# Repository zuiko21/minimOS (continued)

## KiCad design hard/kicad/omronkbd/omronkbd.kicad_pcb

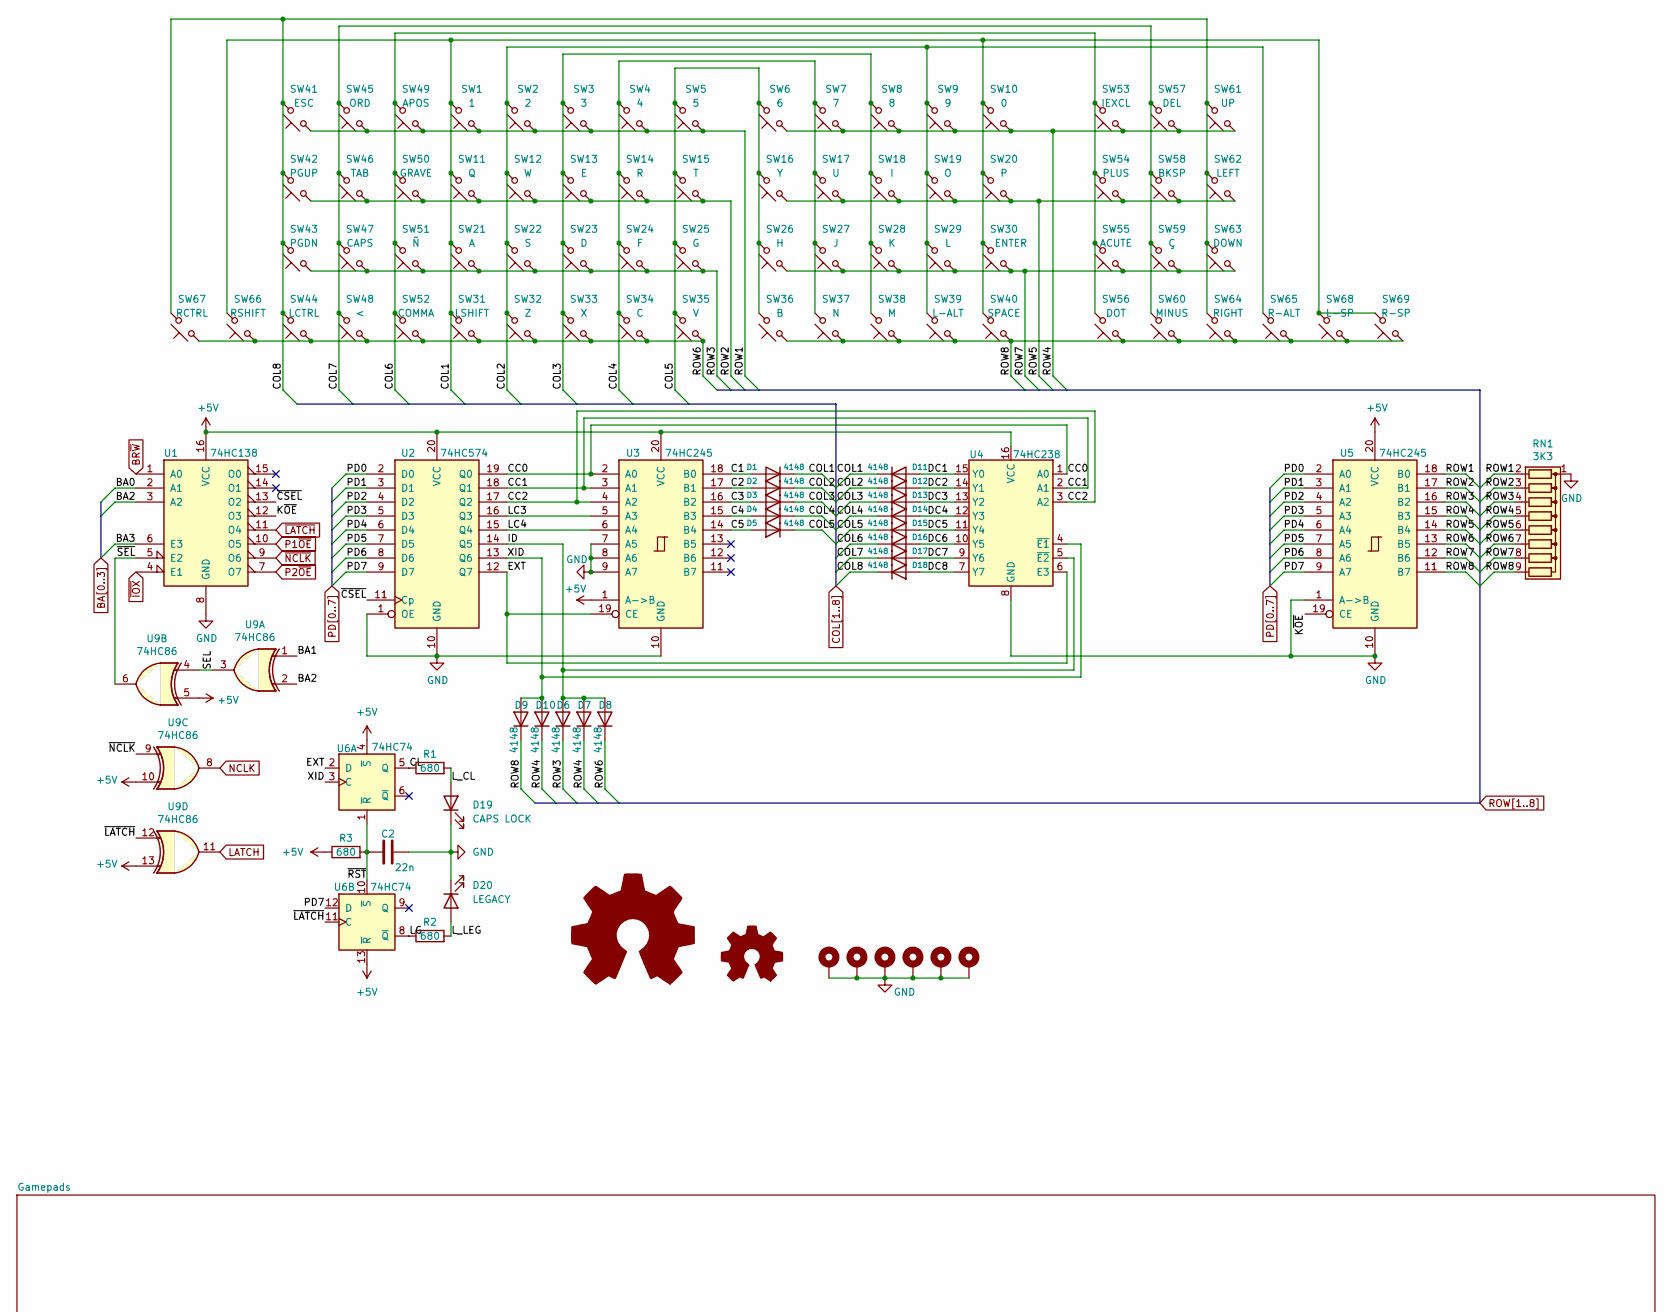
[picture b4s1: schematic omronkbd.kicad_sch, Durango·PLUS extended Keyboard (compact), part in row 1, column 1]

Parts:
C2: 22n; C_Disc_D5.0mm_W2.5mm_P5.00mm
D1, D2, D3, D4, D5, D6, D7, D8, D9, D10, D11, D12, D13, D14, D15, D16, D17, D18: 4148; D_DO-34_SOD68_P7.62mm_Horizontal
D19: CAPS LOCK; LED_D3.0mm
D20: LEGACY; LED_D3.0mm
H1, H2, H3, H4, H5, H6: MountingHole_Pad; MountingHole_3.2mm_M3_DIN965_Pad
LOGO1: OSHW-Logo2_24.3x20mm_SilkScreen
LOGO2: Logo_Open_Hardware_Small; j300
R1, R2, R3: 680; R_Axial_DIN0207_L6.3mm_D2.5mm_P10.16mm_Horizontal
RN1: 3K3; R_Array_SIP9
SW1: 1; SW_SPST_Omron_B3F-40xx
SW2: 2; SW_SPST_Omron_B3F-40xx
SW3: 3; SW_SPST_Omron_B3F-40xx
SW4: 4; SW_SPST_Omron_B3F-40xx
SW5: 5; SW_SPST_Omron_B3F-40xx
SW6: 6; SW_SPST_Omron_B3F-40xx
SW7: 7; SW_SPST_Omron_B3F-40xx
SW8: 8; SW_SPST_Omron_B3F-40xx
SW9: 9; SW_SPST_Omron_B3F-40xx
SW10: 0; SW_SPST_Omron_B3F-40xx
SW11: Q; SW_SPST_Omron_B3F-40xx
SW12: W; SW_SPST_Omron_B3F-40xx
SW13: E; SW_SPST_Omron_B3F-40xx
SW14: R; SW_SPST_Omron_B3F-40xx
SW15: T; SW_SPST_Omron_B3F-40xx
SW16: Y; SW_SPST_Omron_B3F-40xx
SW17: U; SW_SPST_Omron_B3F-40xx
SW18: I; SW_SPST_Omron_B3F-40xx
SW19: O; SW_SPST_Omron_B3F-40xx
SW20: P; SW_SPST_Omron_B3F-40xx
SW21: A; SW_SPST_Omron_B3F-40xx
SW22: S; SW_SPST_Omron_B3F-40xx
SW23: D; SW_SPST_Omron_B3F-40xx
SW24: F; SW_SPST_Omron_B3F-40xx
SW25: G; SW_SPST_Omron_B3F-40xx
SW26: H; SW_SPST_Omron_B3F-40xx
SW27: J; SW_SPST_Omron_B3F-40xx
SW28: K; SW_SPST_Omron_B3F-40xx
SW29: L; SW_SPST_Omron_B3F-40xx
SW30: ENTER; SW_SPST_Omron_B3F-40xx
SW31: LSHIFT; SW_SPST_Omron_B3F-40xx
SW32: Z; SW_SPST_Omron_B3F-40xx
SW33: X; SW_SPST_Omron_B3F-40xx
SW34: C; SW_SPST_Omron_B3F-40xx
SW35: V; SW_SPST_Omron_B3F-40xx
SW36: B; SW_SPST_Omron_B3F-40xx
SW37: N; SW_SPST_Omron_B3F-40xx
SW38: M; SW_SPST_Omron_B3F-40xx
SW39: L-ALT; SW_SPST_Omron_B3F-40xx
SW40: SPACE; SW_SPST_Omron_B3F-40xx
SW41: ESC; SW_SPST_Omron_B3F-40xx
SW42: PGUP; SW_SPST_Omron_B3F-40xx
SW43: PGDN; SW_SPST_Omron_B3F-40xx
SW44: LCTRL; SW_SPST_Omron_B3F-40xx
SW45: ORD; SW_SPST_Omron_B3F-40xx
SW46: TAB; SW_SPST_Omron_B3F-40xx
SW47: CAPS; SW_SPST_Omron_B3F-40xx
SW48: <; SW_SPST_Omron_B3F-40xx
SW49: APOS; SW_SPST_Omron_B3F-40xx
SW50: GRAVE; SW_SPST_Omron_B3F-40xx
SW51: Ñ; SW_SPST_Omron_B3F-40xx
SW52: COMMA; SW_SPST_Omron_B3F-40xx
SW53: IEXCL; SW_SPST_Omron_B3F-40xx
SW54: PLUS; SW_SPST_Omron_B3F-40xx
SW55: ACUTE; SW_SPST_Omron_B3F-40xx
SW56: DOT; SW_SPST_Omron_B3F-40xx
SW57: DEL; SW_SPST_Omron_B3F-40xx
SW58: BKSP; SW_SPST_Omron_B3F-40xx
SW59: Ç; SW_SPST_Omron_B3F-40xx
SW60: MINUS; SW_SPST_Omron_B3F-40xx
SW61: UP; SW_SPST_Omron_B3F-40xx
SW62: LEFT; SW_SPST_Omron_B3F-40xx
SW63: DOWN; SW_SPST_Omron_B3F-40xx
SW64: RIGHT; SW_SPST_Omron_B3F-40xx
SW65: R-ALT; SW_SPST_Omron_B3F-40xx
SW66: RSHIFT; SW_SPST_Omron_B3F-40xx
SW67: RCTRL; SW_SPST_Omron_B3F-40xx
SW68: L-SP; SW_SPST_Omron_B3F-40xx
SW69: R-SP; SW_SPST_Omron_B3F-40xx
U1: 74HC138; DIP-16_W7.62mm_Socket
U2: 74HC574; DIP-20_W7.62mm_Socket
U3, U5: 74HC245; DIP-20_W7.62mm_Socket
U4: 74HC238; DIP-16_W7.62mm_Socket
U6: 74HC74; DIP-14_W7.62mm_Socket
U9: 74HC86; DIP-14_W7.62mm_Socket

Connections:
+5V: R3.1, U1.16 (VCC), U2.20 (VCC), U3.1 (A->B), U3.20 (VCC), U4.16 (VCC), U5.20 (VCC), U6.4 (~S), U6.13 (~R), U6.14 (VCC), U9.5, U9.10, U9.13, U9.14 (VCC); also elsewhere on the board
/C1: D1.2 (A), U3.18 (B0)
/C2: D2.2 (A), U3.17 (B1)
/C3: D3.2 (A), U3.16 (B2)
/C4: D4.2 (A), U3.15 (B3)
/C5: D5.2 (A), U3.14 (B4)
/CC0: U2.19 (Q0), U3.2 (A0), U4.1 (A0)
/CC1: U2.18 (Q1), U3.3 (A1), U4.2 (A1)
/CC2: U2.17 (Q2), U3.4 (A2), U4.3 (A2)
/CL: R1.1, U6.5 (Q)
/DC1: D11.2 (A), U4.15 (Y0)
/DC2: D12.2 (A), U4.14 (Y1)
/DC3: D13.2 (A), U4.13 (Y2)
/DC4: D14.2 (A), U4.12 (Y3)
/DC5: D15.2 (A), U4.11 (Y4)
/DC6: D16.2 (A), U4.10 (Y5)
/DC7: D17.2 (A), U4.9 (Y6)
/DC8: D18.2 (A), U4.7 (Y7)
/EXT: U2.12 (Q7), U3.19 (CE), U4.6 (E3), U6.2 (D)
/ID: D6.2 (A), D7.2 (A), D8.2 (A), U2.14 (Q5), U4.5 (~E2)
/K~OE: U1.12 (O3), U5.19 (CE)
/LC3: U2.16 (Q3), U3.5 (A3)
/LC4: U2.15 (Q4), U3.6 (A4)
/LG: R2.1, U6.8 (~Q)
/L_CL: D19.2 (A), R1.2
/L_LEG: D20.2 (A), R2.2
/SEL: U9.3, U9.4
/XID: D9.2 (A), D10.2 (A), U2.13 (Q6), U4.4 (~E1), U6.3 (C)
/~CSEL: U1.13 (O2), U2.11 (Cp)
/~RST: C2.1, R3.2, U6.1 (~R), U6.10 (~S)
/~SEL: U1.5 (E2), U9.6
BA0: U1.2 (A1); also elsewhere on the board
BA1: U9.1; also elsewhere on the board
BA2: U1.3 (A2), U9.2; also elsewhere on the board
BA3: U1.6 (E3); also elsewhere on the board
BR~W: U1.1 (A0); also elsewhere on the board
COL1: D1.1 (K), D11.1 (K), SW1.2, SW10.2, SW11.2, SW20.2, SW21.2, SW30.2, SW31.2, SW40.2, SW66.2, SW68.2, SW69.2
COL2: D2.1 (K), D12.1 (K), SW2.2, SW9.2, SW12.2, SW19.2, SW22.2, SW29.2, SW32.2, SW39.2, SW65.2
COL3: D3.1 (K), D13.1 (K), SW3.2, SW8.2, SW13.2, SW18.2, SW23.2, SW28.2, SW33.2, SW38.2
COL4: D4.1 (K), D14.1 (K), SW4.2, SW7.2, SW14.2, SW17.2, SW24.2, SW27.2, SW34.2, SW37.2
COL5: D5.1 (K), D15.1 (K), SW5.2, SW6.2, SW15.2, SW16.2, SW25.2, SW26.2, SW35.2, SW36.2
COL6: D16.1 (K), SW49.2, SW50.2, SW51.2, SW52.2, SW53.2, SW54.2, SW55.2, SW56.2
COL7: D17.1 (K), SW45.2, SW46.2, SW47.2, SW48.2, SW57.2, SW58.2, SW59.2, SW60.2
COL8: D18.1 (K), SW41.2, SW42.2, SW43.2, SW44.2, SW61.2, SW62.2, SW63.2, SW64.2, SW67.2
GND: C2.2, D19.1 (K), D20.1 (K), H1.1, H2.1, H3.1, H4.1, H5.1, H6.1, RN1.1 (common), U1.8 (GND), U2.1 (OE), U2.10 (GND), U3.7 (A5), U3.8 (A6), U3.9 (A7), U3.10 (GND), U4.8 (GND), U5.1 (A->B), U5.10 (GND), U6.7 (GND), U9.7 (GND); also elsewhere on the board
LATCH: U9.11; also elsewhere on the board
NCLK: U9.8; also elsewhere on the board
P1~OE: U1.10 (O5); also elsewhere on the board
P2~OE: U1.7 (O7); also elsewhere on the board
PD0: U2.2 (D0), U5.2 (A0); also elsewhere on the board
PD1: U2.3 (D1), U5.3 (A1); also elsewhere on the board
PD2: U2.4 (D2), U5.4 (A2); also elsewhere on the board
PD3: U2.5 (D3), U5.5 (A3); also elsewhere on the board
PD4: U2.6 (D4), U5.6 (A4); also elsewhere on the board
PD5: U2.7 (D5), U5.7 (A5); also elsewhere on the board
PD6: U2.8 (D6), U5.8 (A6); also elsewhere on the board
PD7: U2.9 (D7), U5.9 (A7), U6.12 (D); also elsewhere on the board
ROW1: RN1.2 (R1), SW1.1, SW2.1, SW3.1, SW4.1, SW5.1, SW41.1, SW45.1, SW49.1, U5.18 (B0)
ROW2: RN1.3 (R2), SW11.1, SW12.1, SW13.1, SW14.1, SW15.1, SW42.1, SW46.1, SW50.1, U5.17 (B1)
ROW3: D6.1 (K), RN1.4 (R3), SW21.1, SW22.1, SW23.1, SW24.1, SW25.1, SW43.1, SW47.1, SW51.1, U5.16 (B2)
ROW4: D7.1 (K), D10.1 (K), RN1.5 (R4), SW6.1, SW7.1, SW8.1, SW9.1, SW10.1, SW53.1, SW57.1, SW61.1, U5.15 (B3)
ROW5: RN1.6 (R5), SW16.1, SW17.1, SW18.1, SW19.1, SW20.1, SW54.1, SW58.1, SW62.1, U5.14 (B4)
ROW6: D8.1 (K), RN1.7 (R6), SW31.1, SW32.1, SW33.1, SW34.1, SW35.1, SW44.1, SW48.1, SW52.1, SW66.1, SW67.1, U5.13 (B5)
ROW7: RN1.8 (R7), SW26.1, SW27.1, SW28.1, SW29.1, SW30.1, SW55.1, SW59.1, SW63.1, U5.12 (B6)
ROW8: D9.1 (K), RN1.9 (R8), SW36.1, SW37.1, SW38.1, SW39.1, SW40.1, SW56.1, SW60.1, SW64.1, SW65.1, SW68.1, SW69.1, U5.11 (B7)
~IOX: U1.4 (E1); also elsewhere on the board
~LATCH: U1.11 (O4), U6.11 (C), U9.12; also elsewhere on the board
~NCLK: U1.9 (O6), U9.9; also elsewhere on the board

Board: 2 copper layers, 125 parts (0 on the bottom side), 87 nets, no tracks yet.

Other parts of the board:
C1: 22n; C_Disc_D5.0mm_W2.5mm_P5.00mm
J1: TO COMPUTER; PinSocket_2x08_P2.54mm_Vertical
J2, J3: IOx; IDC-Header_2x08_P2.54mm_Vertical
J101: MD/VCS1; DSUB-9_Male_Horizontal_P2.77x2.84mm_EdgePinOffset4.94mm_Hou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
J102: MD/VCS2; DSUB-9_Male_Horizontal_P2.77x2.84mm_EdgePinOffset4.94mm_Hou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
J201: NES 1; NES gamepad
J202: NES 2; NES gamepad
JP1: MD/VCS; SolderJumper-3_P1.3mm_Bridged12_RoundedPad1.0x1.5mm
RN2, RN101: 22K; R_Array_SIP9
U101, U102: 74HC245; DIP-20_W7.62mm_Socket
U103: 74HC174; DIP-16_W7.62mm_Socket
U201, U202: 74HC595; DIP-16_W7.62mm_Socket

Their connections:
+5V: C1.1, J1.1, J2.1, J3.1, J101.5, J102.5, J201.6, J202.6, JP1.1 (A), RN2.1 (common), RN101.1 (common), U101.20 (VCC), U102.20 (VCC), U103.3 (D0), U103.14 (D5), U103.16 (VCC), U201.10 (~SRCLR), U201.16 (VCC), U202.10 (~SRCLR), U202.16 (VCC); also elsewhere on the board
/Gamepads/VCS: JP1.2 (C), U103.1 (~Mr)
/Gamepads/~A1: U101.11 (B7), U103.7 (Q2)
/Gamepads/~A2: U102.11 (B7), U103.10 (Q3)
/Gamepads/~AB1: J101.6, RN101.8 (R7), U101.13 (B5), U103.6 (D2)
/Gamepads/~AB2: J102.6, RN2.8 (R7), U102.13 (B5), U103.11 (D3)
/Gamepads/~DAT1: J201.1, RN2.2 (R1), U201.14 (SER)
/Gamepads/~DAT2: J202.1, RN2.7 (R6), U202.14 (SER)
/Gamepads/~DN1: J101.2, RN101.4 (R3), U101.17 (B1)
/Gamepads/~DN2: J102.2, RN2.4 (R3), U102.17 (B1)
/Gamepads/~LT1: J101.3, RN101.5 (R4), U101.16 (B2)
/Gamepads/~LT2: J102.3, RN2.5 (R4), U102.16 (B2)
/Gamepads/~RT1: J101.4, RN101.3 (R2), U101.18 (B0)
/Gamepads/~RT2: J102.4, RN2.3 (R2), U102.18 (B0)
/Gamepads/~S1: U101.12 (B6), U103.5 (Q1)
/Gamepads/~S2: U102.12 (B6), U103.12 (Q4)
/Gamepads/~SC1: J101.9, RN101.9 (R8), U101.14 (B4), U103.4 (D1)
/Gamepads/~SC2: J102.9, RN2.9 (R8), U102.14 (B4), U103.13 (D4)
/Gamepads/~UP1: J101.1, RN101.6 (R5), U101.15 (B3)
/Gamepads/~UP2: J102.1, RN2.6 (R5), U102.15 (B3)
BA0: J1.3, J2.3, J3.3; also elsewhere on the board
BA1: J1.5, J2.5, J3.5; also elsewhere on the board
BA2: J1.7, J2.7, J3.7; also elsewhere on the board
BA3: J1.9, J2.9, J3.9; also elsewhere on the board
BR~W: J1.11, J2.11, J3.11; also elsewhere on the board
GND: C1.2, J1.15, J2.15, J3.15, J101.8, J102.8, J201.7, J202.7, JP1.3 (B), U101.1 (A->B), U101.10 (GND), U102.1 (A->B), U102.10 (GND), U103.8 (GND), U201.8 (GND), U202.8 (GND); also elsewhere on the board
LATCH: J201.3, J202.3; also elsewhere on the board
NCLK: J201.5, J202.5, U201.11 (SRCLK), U202.11 (SRCLK); also elsewhere on the board
P1~OE: U101.19 (CE), U201.13 (~OE); also elsewhere on the board
P2~OE: U102.19 (CE), U202.13 (~OE); also elsewhere on the board
PD0: J1.2, J2.2, J3.2, U101.2 (A0), U102.2 (A0), U201.15 (QA), U202.15 (QA); also elsewhere on the board
PD1: J1.4, J2.4, J3.4, U101.3 (A1), U102.3 (A1), U201.2 (QC), U202.2 (QC); also elsewhere on the board
PD2: J1.6, J2.6, J3.6, U101.4 (A2), U102.4 (A2), U201.1 (QB), U202.1 (QB); also elsewhere on the board
PD3: J1.8, J2.8, J3.8, U101.5 (A3), U102.5 (A3), U201.3 (QD), U202.3 (QD); also elsewhere on the board
PD4: J1.10, J2.10, J3.10, U101.6 (A4), U102.6 (A4), U201.5 (QF), U202.5 (QF); also elsewhere on the board
PD5: J1.12, J2.12, J3.12, U101.7 (A5), U102.7 (A5), U201.6 (QG), U202.6 (QG); also elsewhere on the board
PD6: J1.14, J2.14, J3.14, U101.8 (A6), U102.8 (A6), U201.4 (QE), U202.4 (QE); also elsewhere on the board
PD7: J1.16, J2.16, J3.16, U101.9 (A7), U102.9 (A7), U201.7 (QH), U202.7 (QH); also elsewhere on the board
~IOX: J1.13, J2.13, J3.13; also elsewhere on the board
~LATCH: J101.7, J102.7, U103.9 (Cp); also elsewhere on the board
~NCLK: U201.12 (RCLK), U202.12 (RCLK); also elsewhere on the board

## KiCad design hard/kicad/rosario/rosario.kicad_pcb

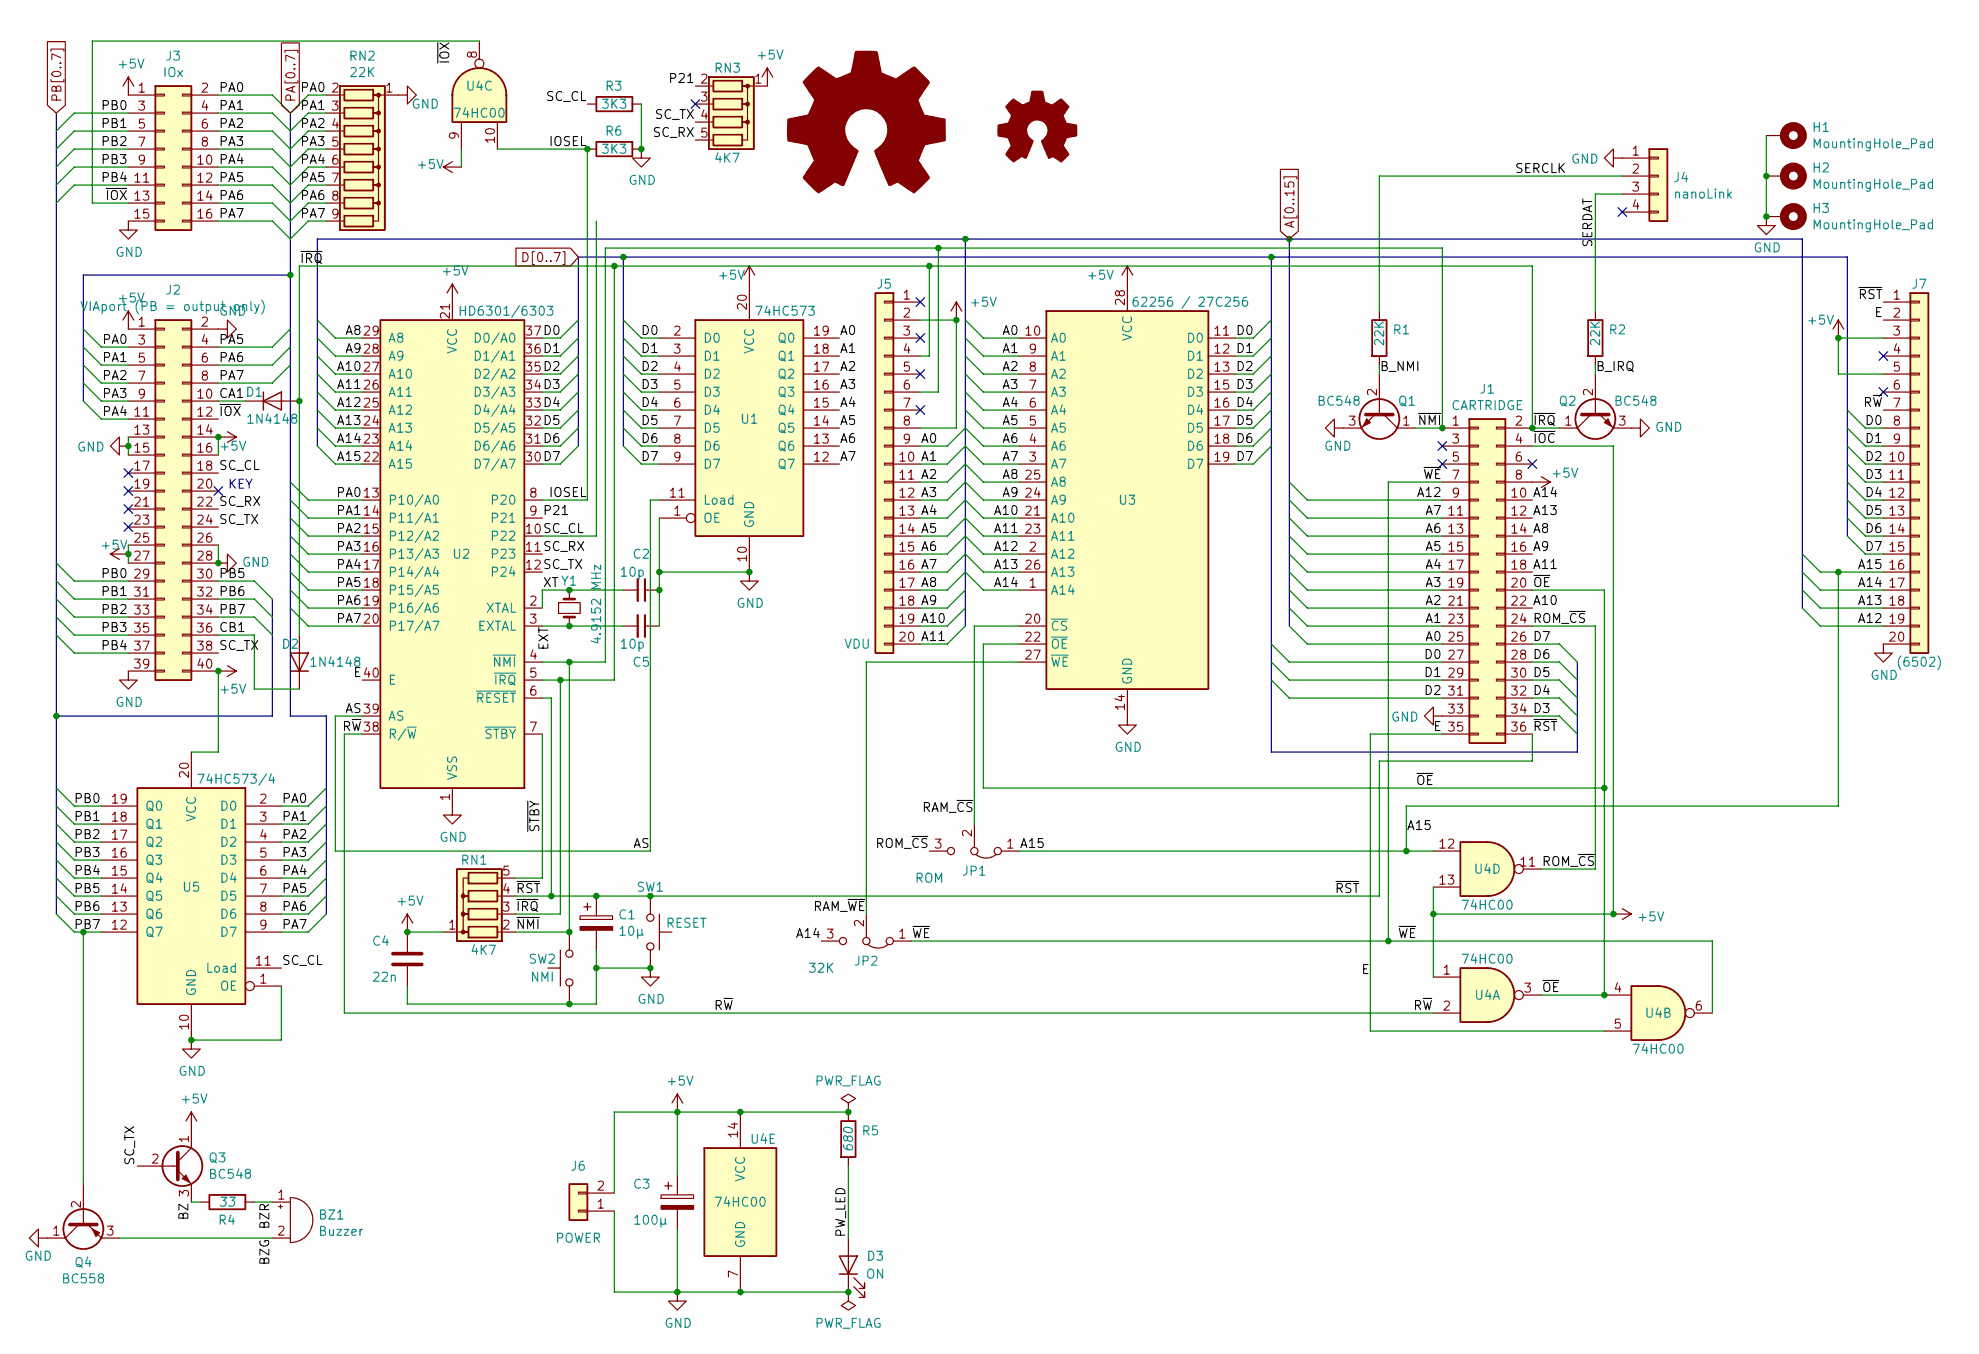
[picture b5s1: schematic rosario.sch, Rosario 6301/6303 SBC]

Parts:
BZ1: Buzzer; Buzzer_12x9.5RM7.6
C1: 10µ; CP_Radial_D4.0mm_P1.50mm
C2, C5: 10p; C_Disc_D3.8mm_W2.6mm_P2.50mm
C3: 100µ; CP_Radial_D4.0mm_P1.50mm
C4: 22n; C_Rect_L7.2mm_W2.5mm_P5.00mm_FKS2_FKP2_MKS2_MKP2
D1, D2: 1N4148; D_DO-35_SOD27_P2.54mm_Vertical_AnodeUp
D3: ON; LED_D3.0mm
H1, H2, H3: MountingHole_Pad; MountingHole_3.2mm_M3_DIN965_Pad
J1: CARTRIDGE; PinSocket_2x18_EDGE
J2: VIAport (PB = output only); IDC-Header_2x20_P2.54mm_Vertical
J3: IOx; IDC-Header_2x08_P2.54mm_Vertical
J4: nanoLink; PinHeader_1x04_P2.54mm_Vertical
J5: VDU; PinSocket_1x20_P2.54mm_Vertical
J6: POWER; JST_EH_S2B-EH_1x02_P2.50mm_Horizontal
J7: (6502); PinSocket_1x20_P2.54mm_Vertical
JP1: ROM; SolderJumper-3_P1.3mm_Bridged12_RoundedPad1.0x1.5mm
JP2: 32K; SolderJumper-3_P1.3mm_Bridged12_RoundedPad1.0x1.5mm
LOGO1: Logo_Open_Hardware_Large; OSHW-Symbol_8.9x8mm_SilkScreen
LOGO2: Logo_Open_Hardware_Small; jaqueria
Q1, Q2, Q3: BC548; TO-92_Inline
Q4: BC558; TO-92_Inline
R1, R2: 22K; R_Axial_DIN0207_L6.3mm_D2.5mm_P2.54mm_Vertical
R3, R6: 3K3; R_Axial_DIN0207_L6.3mm_D2.5mm_P2.54mm_Vertical
R4: 33; R_Axial_DIN0309_L9.0mm_D3.2mm_P2.54mm_Vertical
R5: 680; R_Axial_DIN0207_L6.3mm_D2.5mm_P2.54mm_Vertical
RN1, RN3: 4K7; R_Array_SIP5
RN2: 22K; R_Array_SIP9
SW1: RESET; SW_PUSH_6mm
SW2: NMI; SW_PUSH_6mm
U1: 74HC573; DIP-20_W7.62mm_Socket
U2: HD6301/6303; DIP-40_W15.24mm_Socket
U3: 62256 / 27C256; DIP-28_W15.24mm_Socket
U4: 74HC00; DIP-14_W7.62mm_Socket
U5: 74HC573/4; DIP-20_W7.62mm_Socket
Y1: 4.9152 MHz; Crystal_HC49-U_Vertical

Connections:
/AS: U1.11 (Load), U2.39 (AS)
/BZ: Q3.3 (E), R4.1
/BZG: BZ1.2 (+), Q4.3 (E)
/BZR: BZ1.1 (-), R4.2
/B_IRQ: Q2.2 (B), R2.2
/B_NMI: Q1.2 (B), R1.2
/CA1: D1.1 (K), J2.10
/CB1: D2.1 (K), J2.36
/EXT: C5.2, U2.3 (EXTAL), Y1.2
/IOSEL: R6.1, U2.8 (P20), U4.10
/P21: RN3.2 (R1), U2.9 (P21)
/PW_LED: D3.2 (A), R5.2
/RAM_~CS: JP1.2 (C), U3.20 (~CS)
/RAM_~WE: JP2.2 (C), U3.27 (~WE)
/ROM_~CS: J1.24, JP1.3 (B), U4.11
/R~W: J7.7, U2.38 (R/~W), U4.2
/SC_CL: J2.18, R3.1, U2.10 (P22), U5.11 (Load)
/SC_RX: J2.22, RN3.5 (R4), U2.11 (P23)
/SC_TX: J2.24, J2.38, Q3.2 (B), RN3.4 (R3), U2.12 (P24)
/SERCLK: J4.2, R1.1
/SERDAT: J4.3, R2.1
/XT: C2.2, U2.2 (XTAL), Y1.1
/~IOX: J2.12, J3.13, U4.8
/~IRQ: D1.2 (A), D2.2 (A), J1.2, J5.4, Q2.1 (C), RN1.3 (R2), U2.5 (~IRQ)
/~NMI: J1.1, J5.6, Q1.1 (C), RN1.2 (R1), SW2.2, U2.4 (~NMI)
/~OE: J1.20, U3.22 (~OE), U4.3, U4.4
/~RST: C1.1, J1.36, J7.1, RN1.4 (R3), SW1.2, U2.6 (~RESET)
/~STBY: RN1.5 (R4), U2.7 (~STBY)
/~WE: J1.7, JP2.1 (A), U4.6
A0: J1.25, J5.9, U1.19 (Q0), U3.10 (A0)
A1: J1.23, J5.10, U1.18 (Q1), U3.9 (A1)
A2: J1.21, J5.11, U1.17 (Q2), U3.8 (A2)
A3: J1.19, J5.12, U1.16 (Q3), U3.7 (A3)
A4: J1.17, J5.13, U1.15 (Q4), U3.6 (A4)
A5: J1.15, J5.14, U1.14 (Q5), U3.5 (A5)
A6: J1.13, J5.15, U1.13 (Q6), U3.4 (A6)
A7: J1.11, J5.16, U1.12 (Q7), U3.3 (A7)
A8: J1.14, J5.17, U2.29 (A8), U3.25 (A8)
A9: J1.16, J5.18, U2.28 (A9), U3.24 (A9)
A10: J1.22, J5.19, U2.27 (A10), U3.21 (A10)
A11: J1.18, J5.20, U2.26 (A11), U3.23 (A11)
A12: J1.9, J7.19, U2.25 (A12), U3.2 (A12)
A13: J1.12, J7.18, U2.24 (A13), U3.26 (A13)
A14: J1.10, J7.17, JP2.3 (B), U2.23 (A14), U3.1 (A14)
A15: J7.16, JP1.1 (A), U2.22 (A15), U4.12
D0: J1.27, J7.8, U1.2 (D0), U2.37 (D0/A0), U3.11 (D0)
D1: J1.29, J7.9, U1.3 (D1), U2.36 (D1/A1), U3.12 (D1)
D2: J1.31, J7.10, U1.4 (D2), U2.35 (D2/A2), U3.13 (D2)
D3: J1.34, J7.11, U1.5 (D3), U2.34 (D3/A3), U3.15 (D3)
D4: J1.32, J7.12, U1.6 (D4), U2.33 (D4/A4), U3.16 (D4)
D5: J1.30, J7.13, U1.7 (D5), U2.32 (D5/A5), U3.17 (D5)
D6: J1.28, J7.14, U1.8 (D6), U2.31 (D6/A6), U3.18 (D6)
D7: J1.26, J7.15, U1.9 (D7), U2.30 (D7/A7), U3.19 (D7)
GND: C1.2, C2.1, C3.2, C4.2, C5.1, D3.1 (K), H1.1, H2.1, H3.1, J1.33, J2.2, J2.13, J2.15, J2.26, J2.28, J2.39, J3.15, J4.1, J6.1, J7.20, Q1.3 (E), Q2.3 (E), Q4.1 (C), R3.2, R6.2, RN2.1 (common), SW1.1, SW2.1, U1.1 (OE), U1.10 (GND), U2.1 (VSS), U3.14 (GND), U4.7 (GND), U5.1 (OE), U5.10 (GND)
PA0: J2.3, J3.2, RN2.2 (R1), U2.13 (P10/A0), U5.2 (D0)
PA1: J2.5, J3.4, RN2.3 (R2), U2.14 (P11/A1), U5.3 (D1)
PA2: J2.7, J3.6, RN2.4 (R3), U2.15 (P12/A2), U5.4 (D2)
PA3: J2.9, J3.8, RN2.5 (R4), U2.16 (P13/A3), U5.5 (D3)
PA4: J2.11, J3.10, RN2.6 (R5), U2.17 (P14/A4), U5.6 (D4)
PA5: J2.4, J3.12, RN2.7 (R6), U2.18 (P15/A5), U5.7 (D5)
PA6: J2.6, J3.14, RN2.8 (R7), U2.19 (P16/A6), U5.8 (D6)
PA7: J2.8, J3.16, RN2.9 (R8), U2.20 (P17/A7), U5.9 (D7)
PB0: J2.29, J3.3, U5.19 (Q0)
PB1: J2.31, J3.5, U5.18 (Q1)
PB2: J2.33, J3.7, U5.17 (Q2)
PB3: J2.35, J3.9, U5.16 (Q3)
PB4: J2.37, J3.11, U5.15 (Q4)
PB5: J2.30, U5.14 (Q5)
PB6: J2.32, U5.13 (Q6)
PB7: J2.34, Q4.2 (B), U5.12 (Q7)

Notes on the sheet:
KEY

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
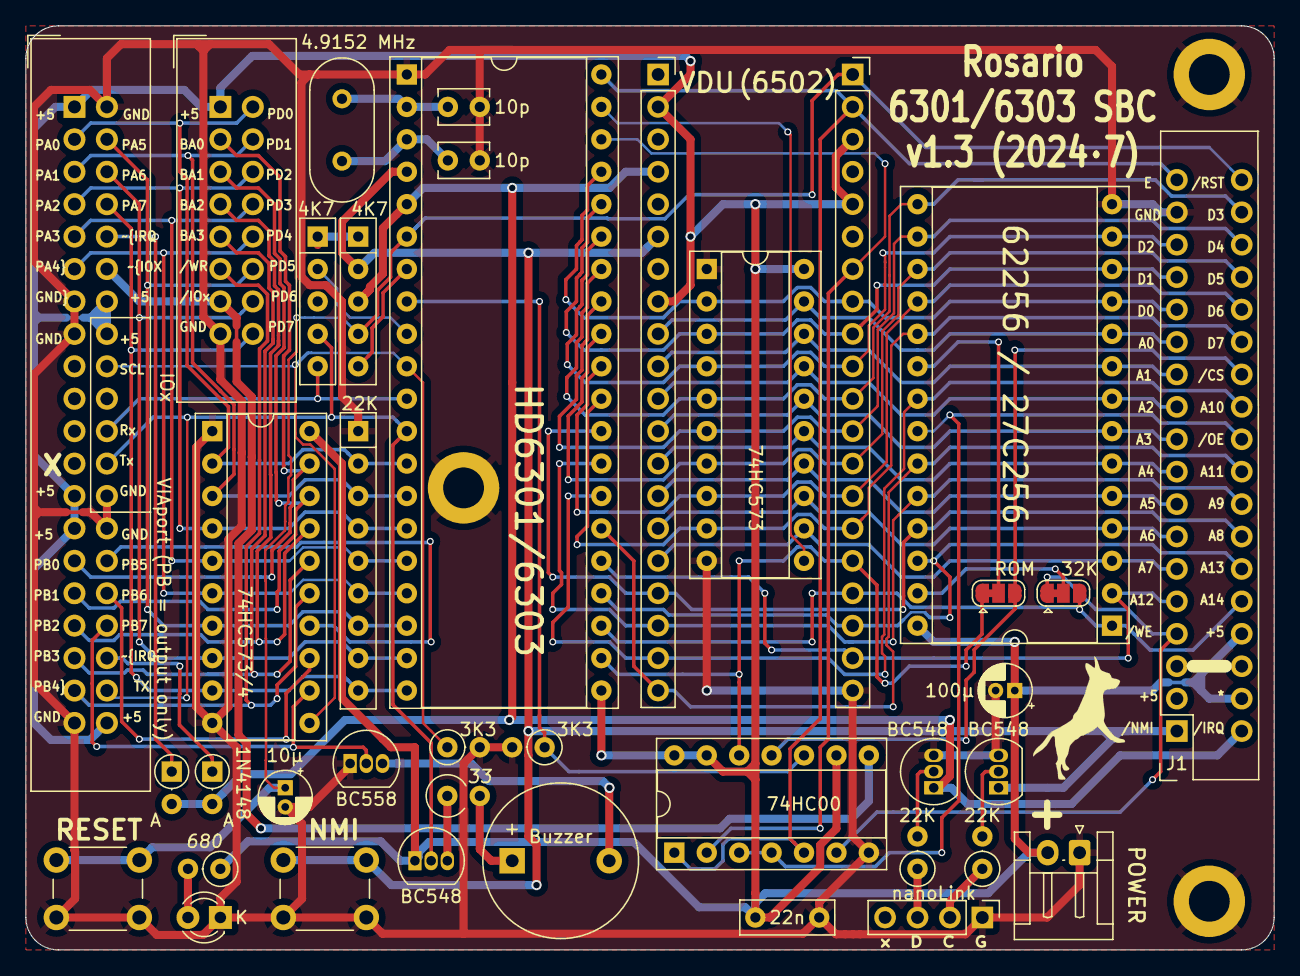
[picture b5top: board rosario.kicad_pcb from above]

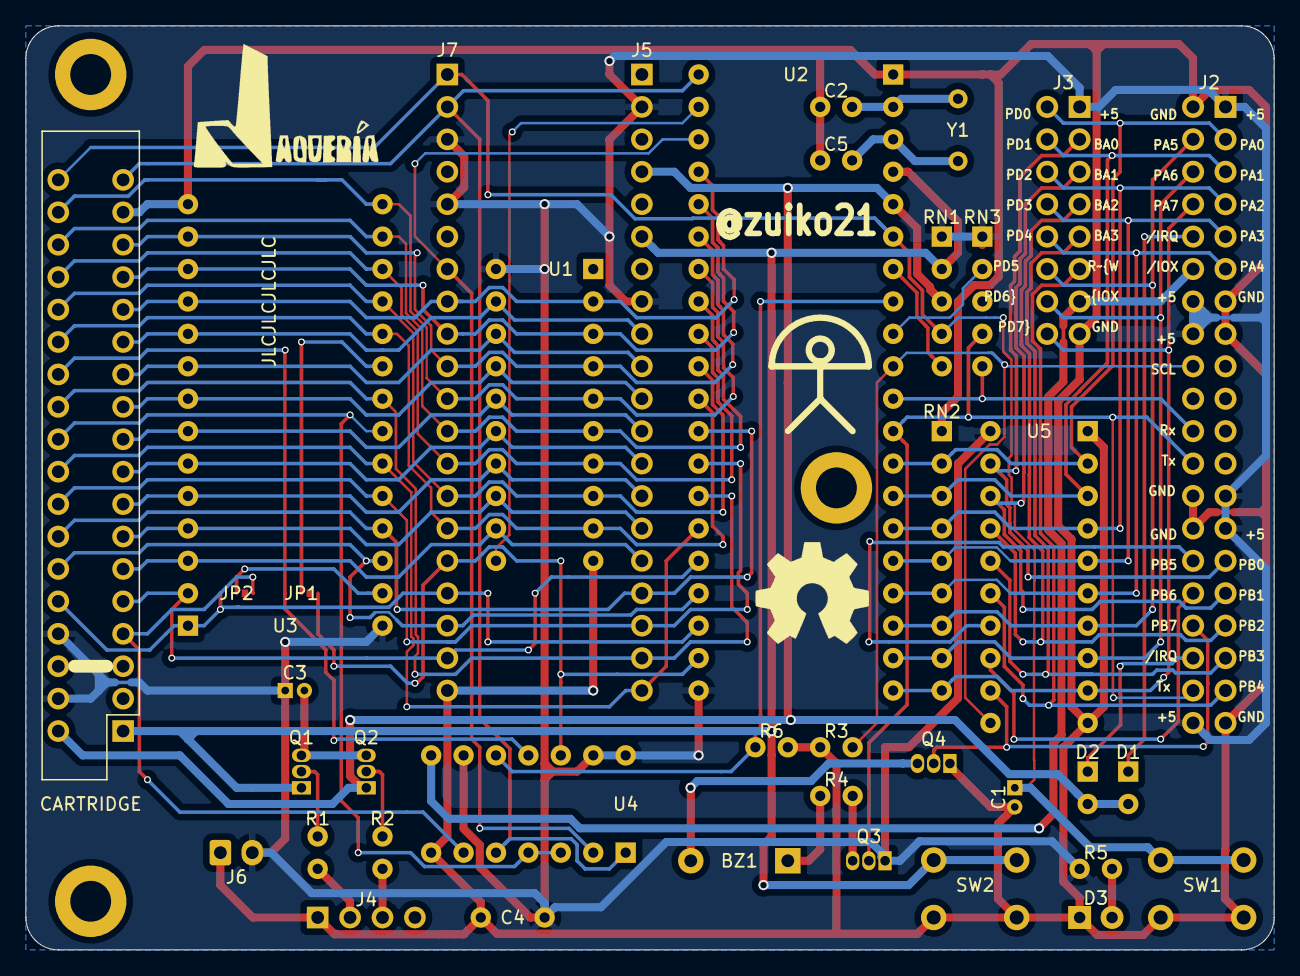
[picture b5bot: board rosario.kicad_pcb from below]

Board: 2 copper layers, 97.8 x 72.4 mm, 44 parts (2 on the bottom side), 72 nets.

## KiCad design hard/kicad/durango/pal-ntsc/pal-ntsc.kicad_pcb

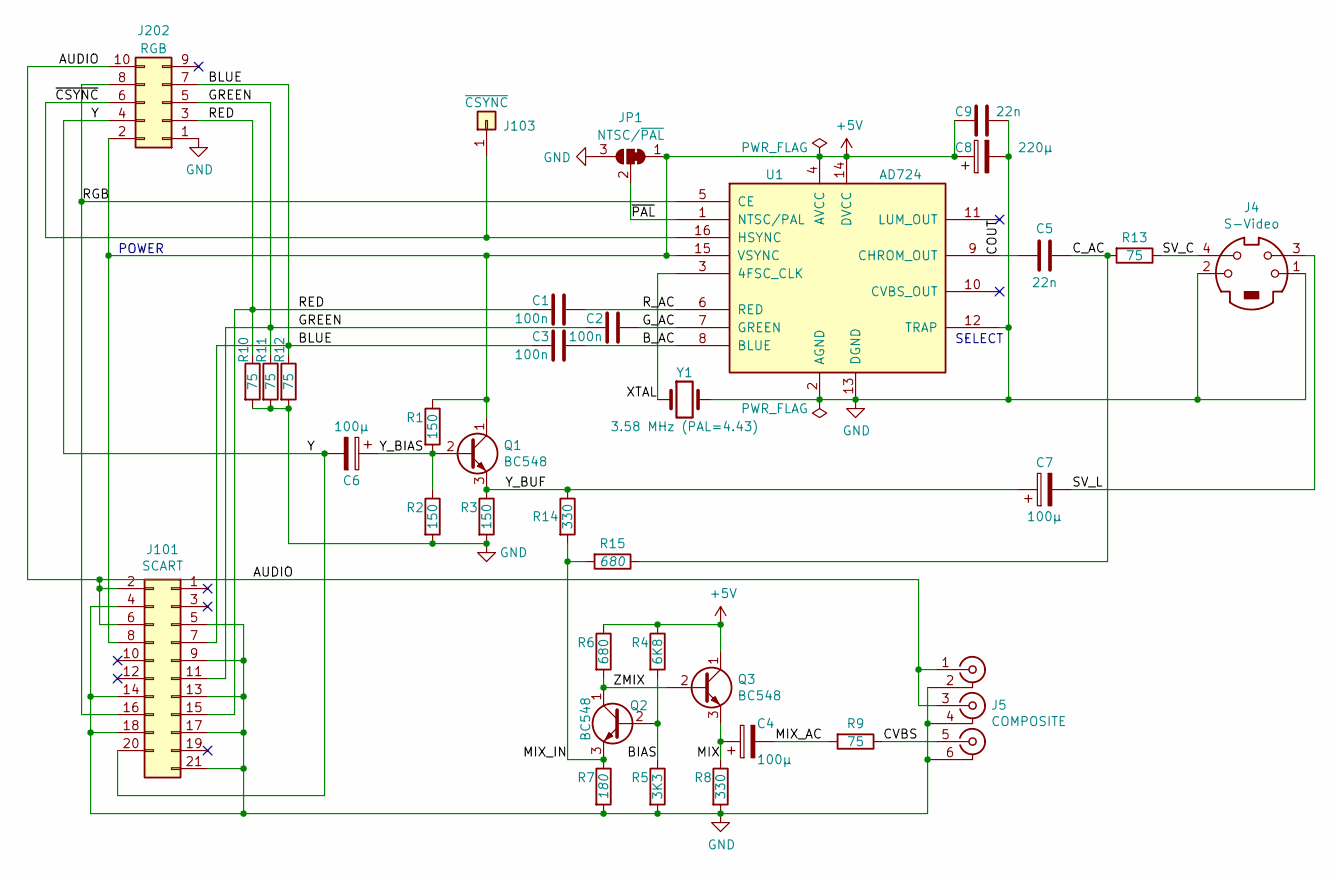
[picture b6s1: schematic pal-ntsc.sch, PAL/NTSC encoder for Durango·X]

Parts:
C1, C2, C3: 100n; C_Rect_L7.2mm_W2.5mm_P5.00mm_FKS2_FKP2_MKS2_MKP2
C4, C6, C7: 100µ; CP_Radial_D4.0mm_P1.50mm
C5, C9: 22n; C_Rect_L7.2mm_W2.5mm_P5.00mm_FKS2_FKP2_MKS2_MKP2
C8: 220µ; CP_Radial_D6.3mm_P2.50mm
J4: S-Video; PinHeader_1x04_P2.54mm_Horizontal
J5: COMPOSITE; 3xRCA
J101: SCART
J103: ~CSYNC; PinHeader_1x01_P2.54mm_Vertical
J202: RGB; PinHeader_2x05_P2.54mm_Horizontal
JP1: NTSC/~PAL; SolderJumper-3_P1.3mm_Bridged12_RoundedPad1.0x1.5mm
Q1, Q2, Q3: BC548; TO-92_Inline
R1, R2, R3: 150; R_Axial_DIN0207_L6.3mm_D2.5mm_P10.16mm_Horizontal
R4: 6K8; R_Axial_DIN0207_L6.3mm_D2.5mm_P10.16mm_Horizontal
R5: 3K3; R_Axial_DIN0207_L6.3mm_D2.5mm_P10.16mm_Horizontal
R6, R15: 680; R_Axial_DIN0207_L6.3mm_D2.5mm_P10.16mm_Horizontal
R7: 180; R_Axial_DIN0207_L6.3mm_D2.5mm_P10.16mm_Horizontal
R8, R14: 330; R_Axial_DIN0207_L6.3mm_D2.5mm_P10.16mm_Horizontal
R9, R10, R11, R12, R13: 75; R_Axial_DIN0207_L6.3mm_D2.5mm_P10.16mm_Horizontal
U1: AD724; SOIC-16W_7.5x10.3mm_P1.27mm
Y1: 3.58 MHz (PAL=4.43); Crystal_HC49-4H_Vertical

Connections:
+5V: C8.1, C9.2, J101.8, J202.2, JP1.1 (A), Q1.1 (C), Q3.1 (C), R1.1, R4.1, R6.1, U1.4 (AVCC), U1.14 (DVCC), U1.15 (VSYNC)
/AUDIO: J5.1 (IN1), J5.3 (IN2), J101.2, J101.6, J202.10
/BIAS: Q2.2 (B), R4.2, R5.1
/BLUE: C3.2, J101.7, J202.7, R12.1
/B_AC: C3.1, U1.8 (BLUE)
/COUT: C5.2, U1.9 (CHROM_OUT)
/CVBS: J5.5 (IN3), R9.1
/C_AC: C5.1, R13.2, R15.1
/GREEN: C2.2, J101.11, J202.5, R11.1
/G_AC: C2.1, U1.7 (GREEN)
/MIX: C4.1, Q3.3 (E), R8.1
/MIX_AC: C4.2, R9.2
/MIX_IN: Q2.3 (E), R7.1, R14.2, R15.2
/RED: C1.2, J101.15, J202.3, R10.1
/RGB: J101.16, J202.8, U1.5 (CE)
/R_AC: C1.1, U1.6 (RED)
/SV_C: J4.4, R13.1
/SV_L: C7.2, J4.3
/XTAL: U1.3 (4FSC_CLK), Y1.1
/Y: C6.2, J101.20, J202.4
/Y_BIAS: C6.1, Q1.2 (B), R1.2, R2.1
/Y_BUF: C7.1, Q1.3 (E), R3.1, R14.1
/ZMIX: Q2.1 (C), Q3.2 (B), R6.2
/~CSYNC: J103.1, J202.6, U1.16 (HSYNC)
/~PAL: JP1.2 (C), U1.1 (NTSC/PAL)
GND: C8.2, C9.1, J4.1, J4.2, J5.2 (GND1), J5.4 (GND2), J5.6 (GND3), J101.4, J101.5, J101.9, J101.13, J101.14, J101.17, J101.18, J101.21, J202.1, JP1.3 (B), R2.2, R3.2, R5.2, R7.2, R8.2, R10.2, R11.2, R12.2, U1.2 (AGND), U1.12 (TRAP), U1.13 (DGND), Y1.2

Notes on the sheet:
SELECT
POWER

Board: 2 copper layers, 35 parts (0 on the bottom side), 26 nets, no tracks yet.
